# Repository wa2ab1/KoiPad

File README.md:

# KoiPad: External Numpad Companion with Rotary Encoder

KoiPad is an external numpad companion with a large rotary encoder, designed for a fun desk setup with fast numeric input.

With its large 4 cm rotary encoder shaped like its eyeball and a USB-C cable inpsired by a fishing line, KoiPad adds a playful companion to your desk.

KoiPad was inspired by the koi shape from Hack Club's Fallout, and I wanted to turn that into something more unique than a typical macropad. When brainstorming case ideas, the ideas for the usb-c cable to be the fishing line at its mouth and the giant knob for its eye made the whole case concept click into place. With my current keyboard being a TKL layout, I also wanted a dedicated numpad which will help improve my number crunching.

## Features:

- 17-key standard numpad layout and num lock
- EC-11 rotary encoder for volume adjustment
- Seeeduino XIAO RP2040
- Standard MX switches with 2u PCB-mount stabilizers
- USB-C connection

## Case

3D print the top plate and bottom case separately, and secure them together using 5 mm M2 screws on the corners. The screws will need to be manually threaded into the bottom case.

### Painting:

The top plate is printed in one color only (red), with the outlines raised for easy brush painting. You'll need 3 colors (yellow, white, black) and red (optional). You can mix the paints for beige and red. First paint the yellow and beige areas, then go over the black outlines and white eye area for a clean finish. You may want to use masking tape to protect the sides of the outlines for a cleaner look. 

## PCB

The KoiPad utilizes standard keyboard switches with 2u PCB mounted stabilizers for the larger keys. After soldering your diodes and switches and snapping on the stabilizers, screw the pcb with 4mm standoffs of M2 size through the countersinks on the bottom of the case and the designated holes on the pcb. Screw these in before screwing on the top plate, and avoid rescrewing the top plate unless necessary to prevent stripping.

## Schematic

## Firmware
The rotary encoder is configured to control system volume up/down, and the keypad includes Enter and Num Lock mappings. You may need to adjust these key codes if your environment handles these special keys differently.

### Libraries used: 
- Keypad
- Adafruit_TinyUSB

### Instructions:
- Find the board manager and look for "Seed SAMD Boards" or "Raspberry Pi Pico/RP2040/RP2350"
- Select XIAO RP2040 board in your COM ports
- Go to Tools -> USB Stack -> select "Adafruit TinyUSB"
- upload the koipad.ino file (hold the B/boot button on the xiao and plug it in, then click upload)

## Credits
3D placeholder/reference models used in renders were sourced from other creators. Final hardware uses real components.

Keycap, switches, stabilizers, standoffs, encoder, and Seeeduino XIAO footprints and 3d models from [ScottoKeebs](https://github.com/joe-scotto/scottokeebs)

[Screws](https://grabcad.com/library/metric-screws-from-m2-x-2-5-to-m2-x-20-1)

[USB-C cable](https://grabcad.com/library/usb-usb-cable-1)

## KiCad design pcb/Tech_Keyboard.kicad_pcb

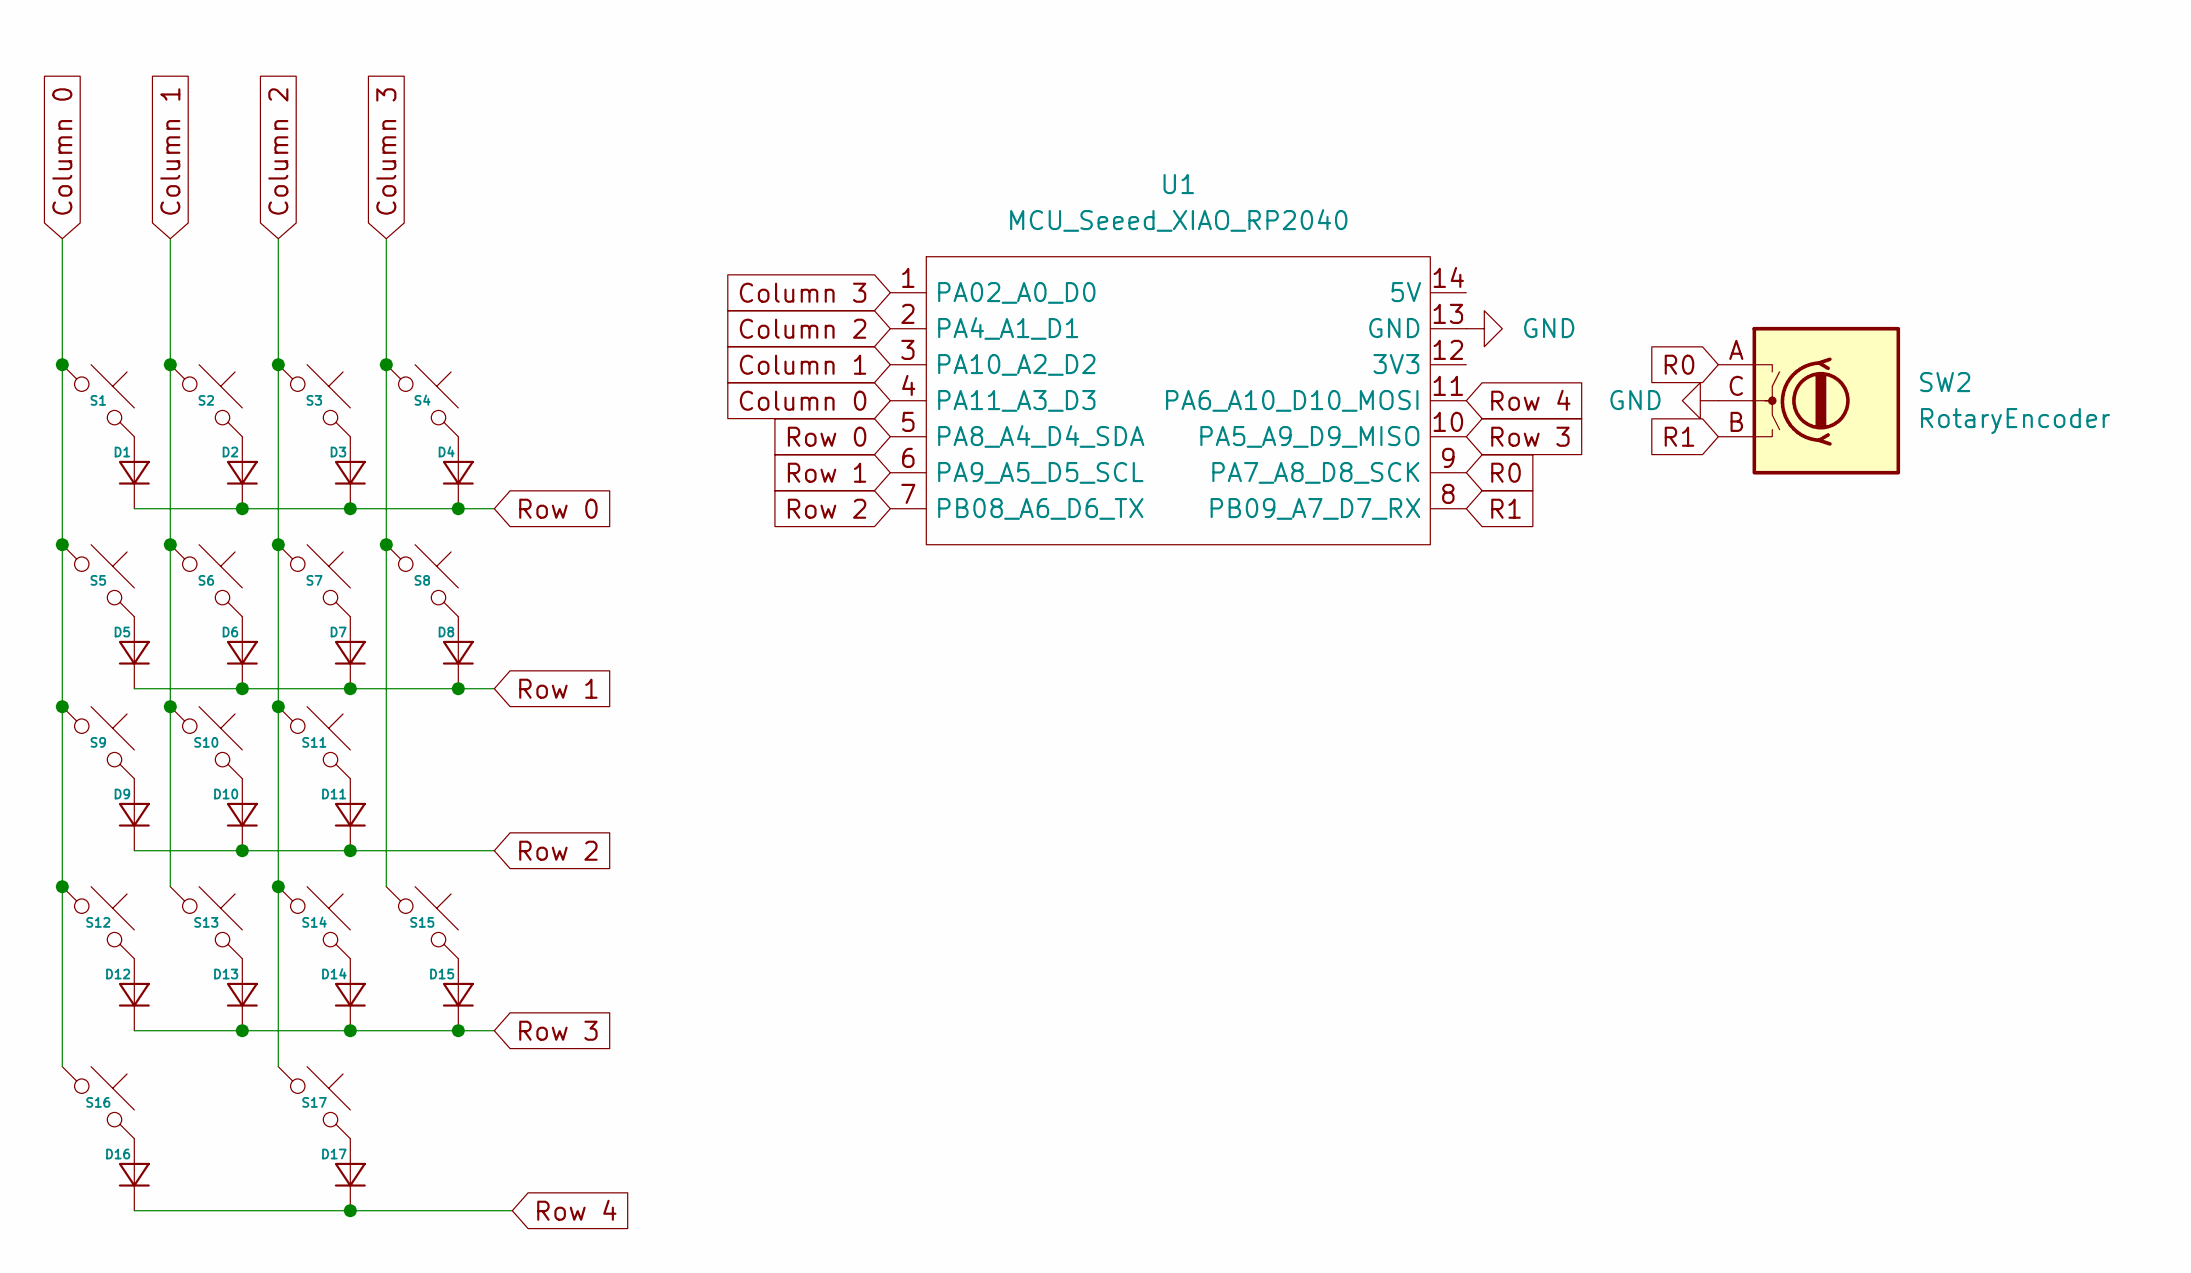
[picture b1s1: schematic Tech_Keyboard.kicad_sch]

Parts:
D1, D2, D3, D4, D5, D6, D7, D8, D9, D10, D11, D12, D13, D14, D15, D16, D17: (no value)
S1, S2, S3, S4, S5, S6, S7, S8, S9, S10, S11, S12, S13, S14, S15, S16, S17: (no value)
SW2: RotaryEncoder
U1: MCU_Seeed_XIAO_RP2040

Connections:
Column 0: S1.1, S5.1, S9.1, S12.1, S16.1, U1.4 (PA11_A3_D3)
Column 1: S2.1, S6.1, S10.1, S13.1, U1.3 (PA10_A2_D2)
Column 2: S3.1, S7.1, S11.1, S14.1, S17.1, U1.2 (PA4_A1_D1)
Column 3: S4.1, S8.1, S15.1, U1.1 (PA02_A0_D0)
GND: SW2.C, U1.13 (GND)
unnamed: D1.2 (A), S1.2
unnamed: D2.2 (A), S2.2
unnamed: D3.2 (A), S3.2
unnamed: D4.2 (A), S4.2
unnamed: D5.2 (A), S5.2
unnamed: D6.2 (A), S6.2
unnamed: D7.2 (A), S7.2
unnamed: D8.2 (A), S8.2
unnamed: D9.2 (A), S9.2
unnamed: D10.2 (A), S10.2
unnamed: D11.2 (A), S11.2
unnamed: D12.2 (A), S12.2
unnamed: D13.2 (A), S13.2
unnamed: D14.2 (A), S14.2
unnamed: D15.2 (A), S15.2
unnamed: D16.2 (A), S16.2
unnamed: D17.2 (A), S17.2
R0: SW2.A, U1.9 (PA7_A8_D8_SCK)
R1: SW2.B, U1.8 (PB09_A7_D7_RX)
Row 0: D1.1 (K), D2.1 (K), D3.1 (K), D4.1 (K), U1.5 (PA8_A4_D4_SDA)
Row 1: D5.1 (K), D6.1 (K), D7.1 (K), D8.1 (K), U1.6 (PA9_A5_D5_SCL)
Row 2: D9.1 (K), D10.1 (K), D11.1 (K), U1.7 (PB08_A6_D6_TX)
Row 3: D12.1 (K), D13.1 (K), D14.1 (K), D15.1 (K), U1.10 (PA5_A9_D9_MISO)
Row 4: D16.1 (K), D17.1 (K), U1.11 (PA6_A10_D10_MOSI)

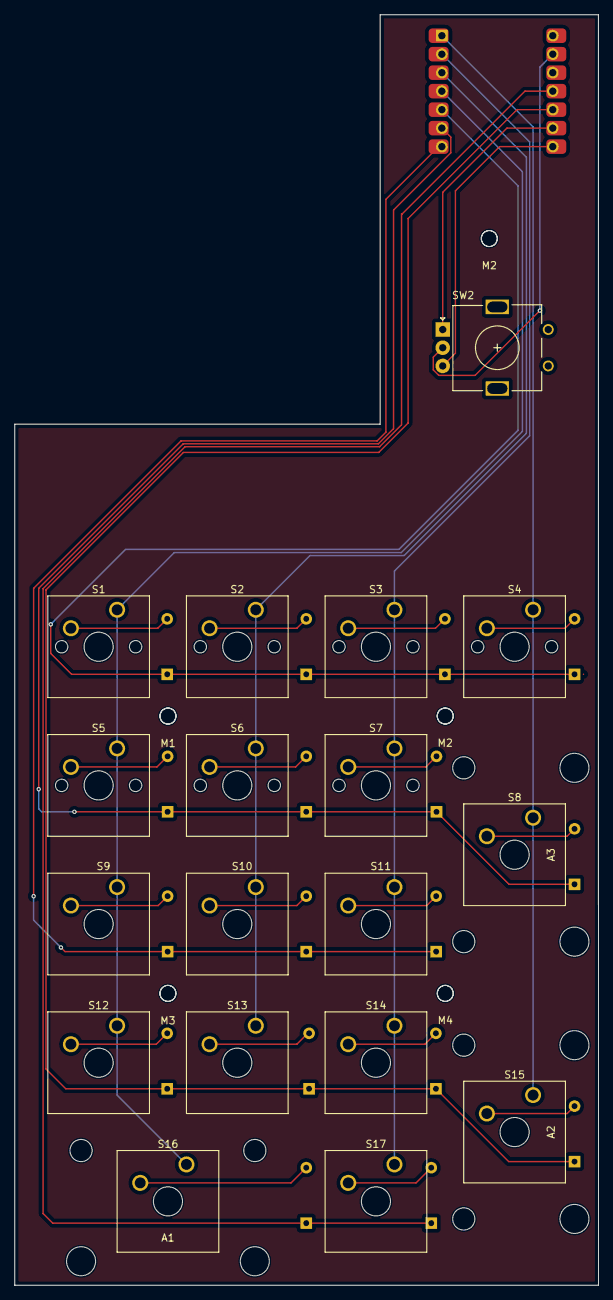
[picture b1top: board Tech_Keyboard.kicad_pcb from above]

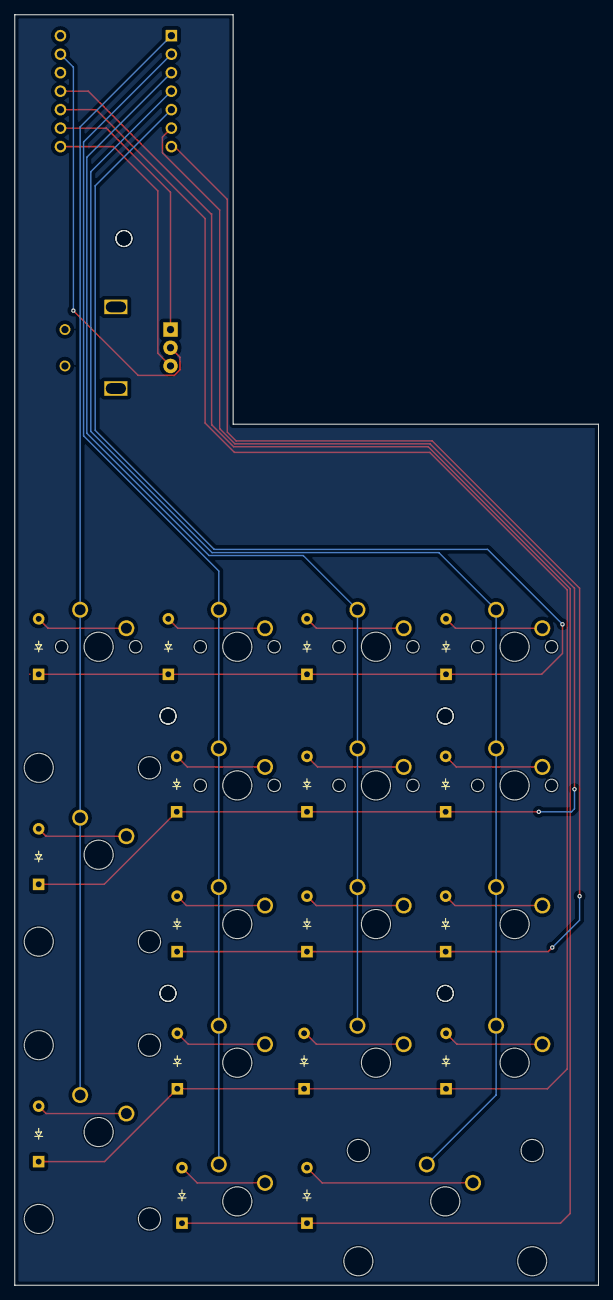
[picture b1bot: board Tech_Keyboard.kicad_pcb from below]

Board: 2 copper layers, 80.2 x 174.6 mm, 45 parts (17 on the bottom side), 29 nets.

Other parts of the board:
A1, A2, A3: Stabilizer_MX_2.00u
M1, M2, M2#2, M3, M4: MountingHole_2.2mm_M2
M3#2: Standoff_M2x4mm

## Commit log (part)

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2026-05-20 updated to fish shape
2026-05-24 Update README.md
    added photo
2026-05-30 Added 3d model and cleaned up files
2026-05-30 update files gerber and f3z
2026-05-30 added stl files
2026-06-02 cleaned up git
2026-06-02 extra git formatting
2026-06-02 updated cad files
2026-06-03 Zine added to readme
2026-06-04 update knob direction
2026-06-05 deleted backups from main github
2026-06-05 update bom
2026-06-05 change bom name
2026-06-05 fixing bom again
2026-06-05 change file nmae
2026-06-05 new bom again
2026-06-05 rename bom
2026-06-05 added zine file
2026-06-05 zine rename
2026-06-06 update bom 1
2026-06-06 bom change 2
2026-06-26 update knob
